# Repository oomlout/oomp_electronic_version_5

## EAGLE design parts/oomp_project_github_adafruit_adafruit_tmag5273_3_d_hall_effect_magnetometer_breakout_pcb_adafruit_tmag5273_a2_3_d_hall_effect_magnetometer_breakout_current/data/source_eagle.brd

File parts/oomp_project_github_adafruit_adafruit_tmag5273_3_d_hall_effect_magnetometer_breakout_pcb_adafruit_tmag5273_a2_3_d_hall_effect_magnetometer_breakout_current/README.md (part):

# Project adafruit/Adafruit-TMAG5273-3D-Hall-Effect-Magnetometer-Breakout-PCB Adafruit TMAG5273 A2 3 D Hall Effect Magnetometer Breakout current

[View the project on GitHub](https://github.com/adafruit/Adafruit-TMAG5273-3D-Hall-Effect-Magnetometer-Breakout-PCB/blob/main/Adafruit%20TMAG5273A2%203D%20Hall%20Effect%20Magnetometer%20Breakout.brd)

[Open the interactive board explorer (GitHub Pages)](https://oomlout.github.io/oomp_electronic_version_5/parts/oomp_project_github_adafruit_adafruit_tmag5273_3_d_hall_effect_magnetometer_breakout_pcb_adafruit_tmag5273_a2_3_d_hall_effect_magnetometer_breakout_current/board_explorer.html)

[Browse this project category](../../navigation/oomp/project/github/adafruit/adafruit_tmag5273_3_d_hall_effect_magnetometer_breakout_pcb/adafruit_tmag5273_a2_3_d_hall_effect_magnetometer_breakout/README.md)

Project adafruit/Adafruit-TMAG5273-3D-Hall-Effect-Magnetometer-Breakout-PCB Adafruit TMAG5273 A2 3 D Hall Effect Magnetometer Breakout current is a KiCad project containing 57 extracted component records. The catalogue matcher linked 14 physical placements to OOMP parts.

## Project snapshot

| Item | Count |
| --- | ---: |
| Components | 57 |
| PCB footprints | 39 |
| Mounting and locating holes | 4 |
| Matched OOMP mounting-hole items | 4 |
| Schematic symbols | 44 |
| Matched OOMP components | 14 |
| Unmatched physical components | 17 |
| Front-side placements | 23 |
| Back-side placements | 4 |
| Project version | `current` |
| Git ref | `main` |

## Board

[Original KiCad files](https://github.com/oomlout/oomp_electronic_version_5/tree/main/parts/oomp_project_github_adafruit_adafruit_tmag5273_3_d_hall_effect_magnetometer_breakout_pcb_adafruit_tmag5273_a2_3_d_hall_effect_magnetometer_breakout_current/data/original) · [OOMP KiCad design and local libraries](https://github.com/oomlout/oomp_electronic_version_5/tree/main/parts/oomp_project_github_adafruit_adafruit_tmag5273_3_d_hall_effect_magnetometer_breakout_pcb_adafruit_tmag5273_a2_3_d_hall_effect_magnetometer_breakout_current/data/oomp_design) · [Conversion / skipped-item report](https://github.com/oomlout/oomp_electronic_version_5/blob/main/parts/oomp_project_github_adafruit_adafruit_tmag5273_3_d_hall_effect_magnetometer_breakout_pcb_adafruit_tmag5273_a2_3_d_hall_effect_magnetometer_breakout_current/data/oomp_design/conversion_report.yaml)

The OOMP design is a separate copy. Only symbols and footprints verified against unchanged installed KiCad masters are replaced; custom and modified items are retained.

- Approximate size: **25.4 mm × 17.78 mm**
- Outline source: `KiCad Edge.Cuts`
- Placement drawing: [view `board.svg`](https://github.com/oomlout/oomp_electronic_version_5/blob/main/parts/oomp_project_github_adafruit_adafruit_tmag5273_3_d_hall_effect_magnetometer_breakout_pcb_adafruit_tmag5273_a2_3_d_hall_effect_magnetometer_breakout_current/data/generated_data/src/board.svg)
- PNG placement drawing: [view `board.png`](https://github.com/oomlout/oomp_electronic_version_5/blob/main/parts/oomp_project_github_adafruit_adafruit_tmag5273_3_d_hall_effect_magnetometer_breakout_pcb_adafruit_tmag5273_a2_3_d_hall_effect_magnetometer_breakout_current/data/generated_data/src/board.png)
- 300-pixel placement preview: [view `board_300.png`](https://github.com/oomlout/oomp_electronic_version_5/blob/main/parts/oomp_project_github_adafruit_adafruit_tmag5273_3_d_hall_effect_magnetometer_breakout_pcb_adafruit_tmag5273_a2_3_d_hall_effect_magnetometer_breakout_current/data/generated_data/src/board_300.png)
- Placement drawing with pin names: [view `board_pins.svg`](https://github.com/oomlout/oomp_electronic_version_5/blob/main/parts/oomp_project_github_adafruit_adafruit_tmag5273_3_d_hall_effect_magnetometer_breakout_pcb_adafruit_tmag5273_a2_3_d_hall_effect_magnetometer_breakout_current/data/generated_data/src/board_pins.svg)
- PNG drawing with pin names: [view `board_pins.png`](https://github.com/oomlout/oomp_electronic_version_5/blob/main/parts/oomp_project_github_adafruit_adafruit_tmag5273_3_d_hall_effect_magnetometer_breakout_pcb_adafruit_tmag5273_a2_3_d_hall_effect_magnetometer_breakout_current/data/generated_data/src/board_pins.png)
- 300-pixel pin preview: [view `board_pins_300.png`](https://github.com/oomlout/oomp_electronic_version_5/blob/main/parts/oomp_project_github_adafruit_adafruit_tmag5273_3_d_hall_effect_magnetometer_breakout_pcb_adafruit_tmag5273_a2_3_d_hall_effect_magnetometer_breakout_current/data/generated_data/src/board_pins_300.png)
- Bottom placement drawing: [view `board_bottom.svg`](https://github.com/oomlout/oomp_electronic_version_5/blob/main/parts/oomp_project_github_adafruit_adafruit_tmag5273_3_d_hall_effect_magnetometer_breakout_pcb_adafruit_tmag5273_a2_3_d_hall_effect_magnetometer_breakout_current/data/generated_data/src/board_bottom.svg)
- Bottom PNG placement drawing: [view `board_bottom.png`](https://github.com/oomlout/oomp_electronic_version_5/blob/main/parts/oomp_project_github_adafruit_adafruit_tmag5273_3_d_hall_effect_magnetometer_breakout_pcb_adafruit_tmag5273_a2_3_d_hall_effect_magnetometer_breakout_current/data/generated_data/src/board_bottom.png)
- 300-pixel bottom preview: [view `board_bottom_300.png`](https://github.com/oomlout/oomp_electronic_version_5/blob/main/parts/oomp_project_github_adafruit_adafruit_tmag5273_3_d_hall_effect_magnetometer_breakout_pcb_adafruit_tmag5273_a2_3_d_hall_effect_magnetometer_breakout_current/data/generated_data/src/board_bottom_300.png)
- Bottom placement drawing with pin names: [view `board_pins_bottom.svg`](https://github.com/oomlout/oomp_electronic_version_5/blob/main/parts/oomp_project_github_adafruit_adafruit_tmag5273_3_d_hall_effect_magnetometer_breakout_pcb_adafruit_tmag5273_a2_3_d_hall_effect_magnetometer_breakout_current/data/generated_data/src/board_pins_bottom.svg)
- Bottom PNG drawing with pin names: [view `board_pins_bottom.png`](https://github.com/oomlout/oomp_electronic_version_5/blob/main/parts/oomp_project_github_adafruit_adafruit_tmag5273_3_d_hall_effect_magnetometer_breakout_pcb_adafruit_tmag5273_a2_3_d_hall_effect_magnetometer_breakout_current/data/generated_data/src/board_pins_bottom.png)
- 300-pixel bottom pin preview: [view `board_pins_bottom_300.png`](https://github.com/oomlout/oomp_electronic_version_5/blob/main/parts/oomp_project_github_adafruit_adafruit_tmag5273_3_d_hall_effect_magnetometer_breakout_pcb_adafruit_tmag5273_a2_3_d_hall_effect_magnetometer_breakout_current/data/generated_data/src/board_pins_bottom_300.png)
- Mechanical drawing: [view `board_mechanical.svg`](https://github.com/oomlout/oomp_electronic_version_5/blob/main/parts/oomp_project_github_adafruit_adafruit_tmag5273_3_d_hall_effect_magnetometer_breakout_pcb_adafruit_tmag5273_a2_3_d_hall_effect_magnetometer_breakout_current/data/generated_data/src/board_mechanical.svg)
- Mechanical PNG: [view `board_mechanical.png`](https://github.com/oomlout/oomp_electronic_version_5/blob/main/parts/oomp_project_github_adafruit_adafruit_tmag5273_3_d_hall_effect_magnetometer_breakout_pcb_adafruit_tmag5273_a2_3_d_hall_effect_magnetometer_breakout_current/data/generated_data/src/board_mechanical.png)
- 300-pixel mechanical preview: [view `board_mechanical_300.png`](https://github.com/oomlout/oomp_electronic_version_5/blob/main/parts/oomp_project_github_adafruit_adafruit_tmag5273_3_d_hall_effect_magnetometer_breakout_pcb_adafruit_tmag5273_a2_3_d_hall_effect_magnetometer_breakout_current/data/generated_data/src/board_mechanical_300.png)
- Open the board explorer on GitHub Pages: [explore this board](https://oomlout.github.io/oomp_electronic_version_5/parts/oomp_project_github_adafruit_adafruit_tmag5273_3_d_hall_effect_magnetometer_breakout_pcb_adafruit_tmag5273_a2_3_d_hall_effect_magnetometer_breakout_current/board_explorer.html)
- InteractiveHtmlBom generation is configured; install KiCad or set `KICAD_PYTHON` to its bundled Python to build `data/interactivehtmlbom/ibom.html`.

## Board with pins

## Bottom board with pins

The bottom view is mirrored horizontally so it is shown as viewed from beneath the assembled board.

## Mechanical layer

The table uses a board-relative origin at the minimum X/Y point of `Edge.Cuts`. This point is shown as **0,0** in the mechanical drawing; X increases right and Y increases down. Original KiCad coordinates are retained alongside it.

### Diameter 2.5 mm holes

| OOMP reference | Source | Name | Classification | Role | Board X (mm) | Board Y (mm) | OOMP part |
| --- | --- | --- | --- | --- | ---: | ---: | --- |
| `MH1` | `U$1` | Mounting Hole 2.5 mm Round Plated | `mechanical / mounting_hole / 2_5_mm / round / plated` | mounting | 2.540 | 2.540 | [`mechanical_mounting_hole_2_5_mm_round_plated`](https://github.com/oomlout/oomp_electronic_version_5/tree/main/parts/mechanical_mounting_hole_2_5_mm_round_plated) |
| `MH2` | `U$17` | Mounting Hole 2.5 mm Round Plated | `mechanical / mounting_hole / 2_5_mm / round / plated` | mounting | 22.860 | 2.540 | [`mechanical_mounting_hole_2_5_mm_round_plated`](https://github.com/oomlout/oomp_electronic_version_5/tree/main/parts/mechanical_mounting_hole_2_5_mm_round_plated) |
| `MH3` | `U$19` | Mounting Hole 2.5 mm Round Plated | `mechanical / mounting_hole / 2_5_mm / round / plated` | mounting | 2.540 | 15.240 | [`mechanical_mounting_hole_2_5_mm_round_plated`](https://github.com/oomlout/oomp_electronic_version_5/tree/main/parts/mechanical_mounting_hole_2_5_mm_round_plated) |
| `MH4` | `U$21` | Mounting Hole 2.5 mm Round Plated | `mechanical / mounting_hole / 2_5_mm / round / plated` | mounting | 22.860 | 15.240 | [`mechanical_mounting_hole_2_5_mm_round_plated`](https://github.com/oomlout/oomp_electronic_version_5/tree/main/parts/mechanical_mounting_hole_2_5_mm_round_plated) |

## Bill of materials

| References | Quantity | Description | Value | Footprint | OOMP part |
| --- | ---: | --- | --- | --- | --- |
| C1 | 1 | Capacitor 100 nF 0603 | 0.1uF | `0603-NO` | [`electronic_capacitor_0603_100_nano_farad`](https://github.com/oomlout/oomp_electronic_version_5/tree/main/parts/electronic_capacitor_0603_100_nano_farad) |
| C2, C3 | 2 | Capacitor 10 uF 0805 | 10uF | `0805-NO` | [`electronic_capacitor_0805_10_micro_farad`](https://github.com/oomlout/oomp_electronic_version_5/tree/main/parts/electronic_capacitor_0805_10_micro_farad) |
| CONN3, CONN4 | 2 | Connector JST Sh SM04B-SRSS-TB | STEMMA_I2C_QT | `JST_SH4` | [`electronic_connector_jst_sh_1_mm_pitch_surface_mount_right_angle_4_pin_jst_sm04b_srss_tb`](https://github.com/oomlout/oomp_electronic_version_5/tree/main/parts/electronic_connector_jst_sh_1_mm_pitch_surface_mount_right_angle_4_pin_jst_sm04b_srss_tb) |
| D1 | 1 | LED Green 0603 | GREEN | `CHIPLED_0603_NOOUTLINE` | [`electronic_led_0603_green`](https://github.com/oomlout/oomp_electronic_version_5/tree/main/parts/electronic_led_0603_green) |
| IC2 | 1 | TMAG5273A2 | TMAG5273A2 | `SOT23-6` | unmatched |
| JP1 | 1 | Connector Header 2.54-1x6P直针 |  | `1X06_ROUND_70` | [`electronic_connector_header_2_54_mm_pitch_through_hole_6_pin`](https://github.com/oomlout/oomp_electronic_version_5/tree/main/parts/electronic_connector_header_2_54_mm_pitch_through_hole_6_pin) |
| PLABEL0 | 1 | PLABEL0 |  | `PLABEL0` | unmatched |
| PLABEL1 | 1 | PLABEL1 |  | `PLABEL1` | unmatched |
| PLABEL2 | 1 | PLABEL2 |  | `PLABEL2` | unmatched |
| PLABEL3 | 1 | PLABEL3 |  | `PLABEL3` | unmatched |
| PLABEL4 | 1 | PLABEL4 |  | `PLABEL4` | unmatched |
| PLABEL6 | 1 | PLABEL6 |  | `PLABEL6` | unmatched |
| PLABEL7 | 1 | PLABEL7 |  | `PLABEL7` | unmatched |
| PLABEL8 | 1 | PLABEL8 |  | `PLABEL8` | unmatched |
| PLABEL9 | 1 | PLABEL9 |  | `PLABEL9` | unmatched |
| PLABEL10 | 1 | PLABEL10 |  | `PLABEL10` | unmatched |
| PLABEL13 | 1 | PLABEL13 |  | `PLABEL13` | unmatched |
| PLABEL14 | 1 | PLABEL14 |  | `PLABEL14` | unmatched |
| PLABEL15 | 1 | PLABEL15 |  | `PLABEL15` | unmatched |
| PLABEL16 | 1 | PLABEL16 |  | `PLABEL16` | unmatched |
| PLABEL17 | 1 | PLABEL17 |  | `PLABEL17` | unmatched |
| Q2 | 1 | Transistor Mosfet N Channel Dual SOT 363 6 | BSS138 | `SOT363` | [`electronic_transistor_sot_363_6_mosfet_n_channel_dual`](https://github.com/oomlout/oomp_electronic_version_5/tree/main/parts/electronic_transistor_sot_363_6_mosfet_n_channel_dual) |
| R1 | 1 | Resistor 10000 Ohm 0603 | 10K | `0603-NO` | [`electronic_resistor_0603_10000_ohm`](https://github.com/oomlout/oomp_electronic_version_5/tree/main/parts/electronic_resistor_0603_10000_ohm) |
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
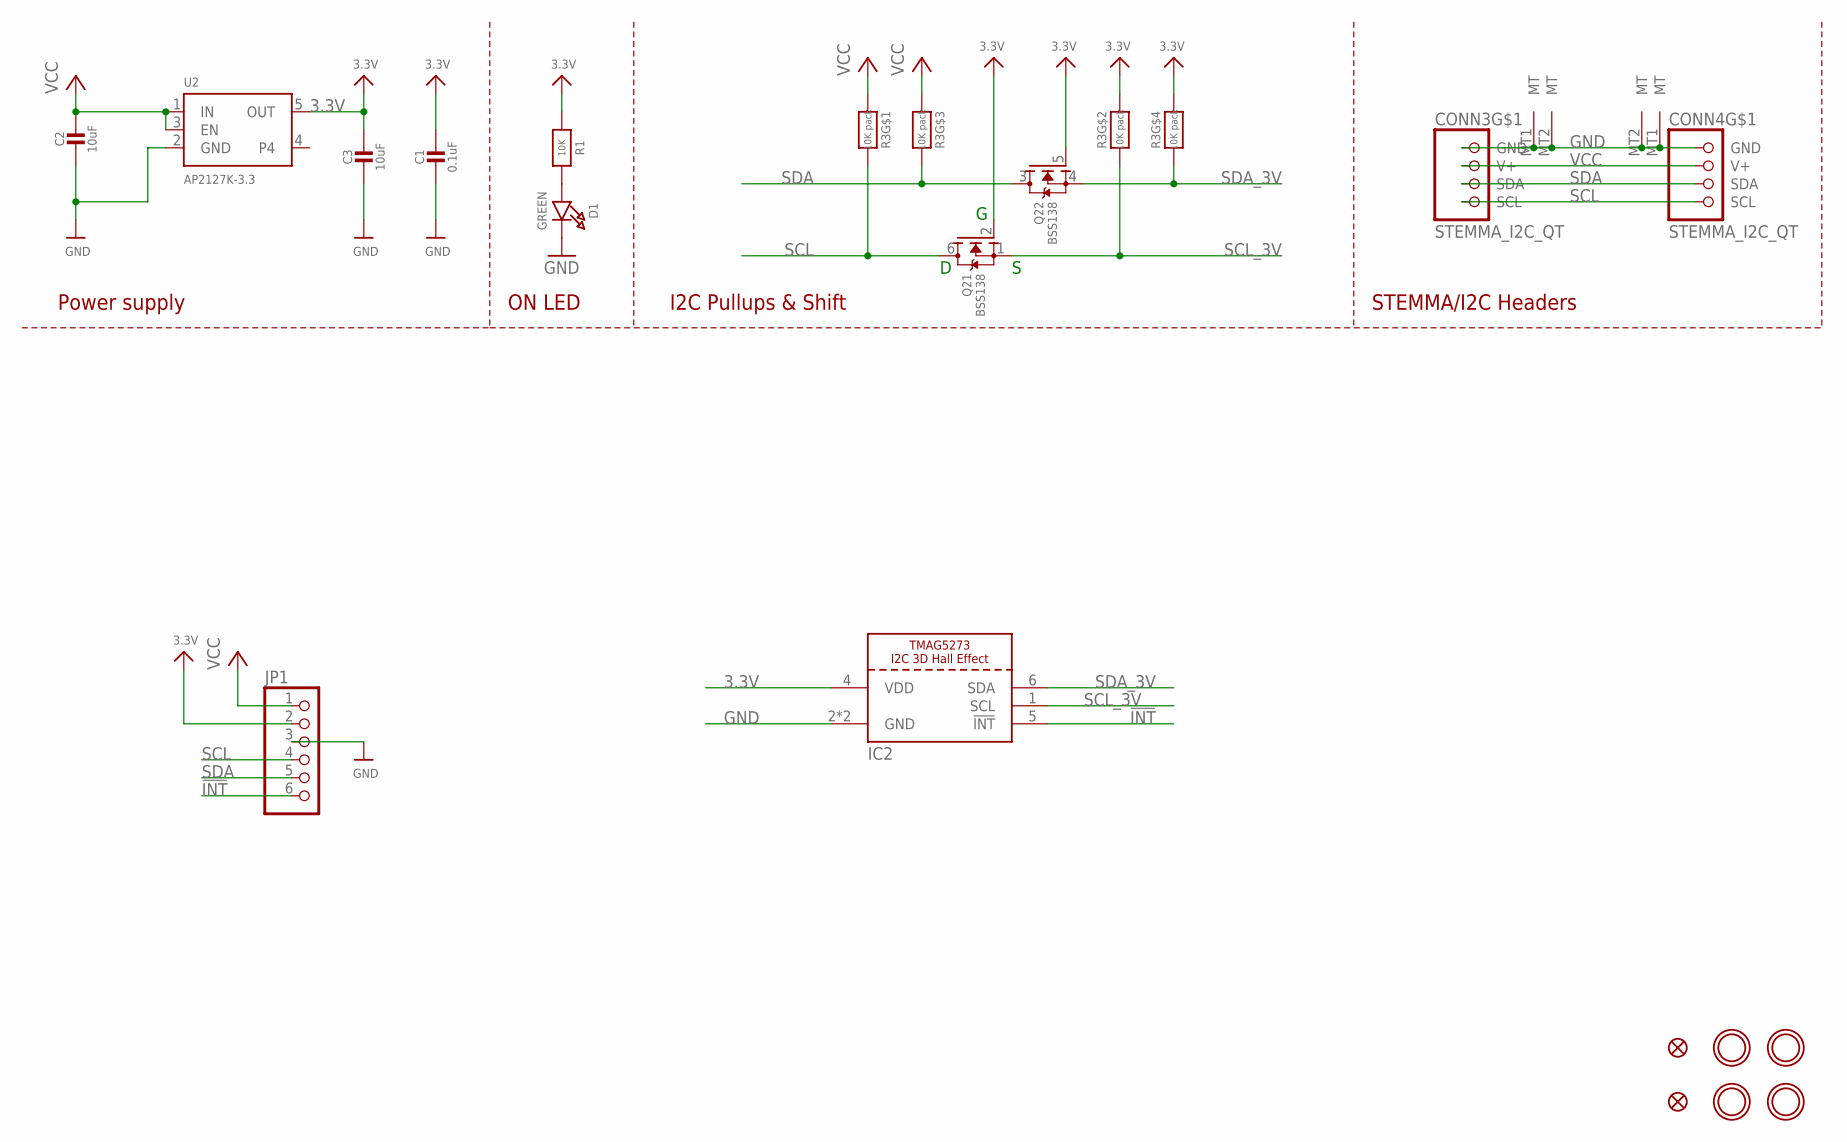
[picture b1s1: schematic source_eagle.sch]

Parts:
C1: 0.1uF; 0603-NO
C2, C3: 10uF; 0805-NO
CONN3, CONN4: STEMMA_I2C_QT; JST_SH4
D1: GREEN; CHIPLED_0603_NOOUTLINE
FID3, FID4: FIDUCIAL_0.5MM
IC2: TMAG5273A2; SOT23-6
JP1: HEADER-1X670MIL; 1X06_ROUND_70
Q2: BSS138; SOT363
R1: 10K; 0603-NO
R3: 10K pack; RESPACK_4X0603
U2: AP2127K-3.3; SOT23-5
U$1, U$17, U$19, U$21: MOUNTINGHOLE2.5; MOUNTINGHOLE_2.5_PLATED

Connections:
3.3V: C1.1, C3.1, IC2.4 (VDD), JP1.2, Q2.2 (G), Q2.5 (G), R1.1, R3.2 (1), R3.4 (1), U2.5 (OUT)
!INT: IC2.5 (!INT), JP1.6
GND: C1.2, C2.2, C3.2, CONN3.1 (GND), CONN3.MT1 (MT), CONN3.MT2 (MT), CONN4.1 (GND), CONN4.MT1 (MT), CONN4.MT2 (MT), D1.C, IC2.2 (GND), IC2.3 (GND), JP1.3, U2.2 (GND)
unnamed: D1.A, R1.2
SCL: CONN3.4 (SCL), CONN4.4 (SCL), JP1.4, Q2.6 (D), R3.8 (2)
SCL_3V: IC2.1 (SCL), Q2.1 (S), R3.7 (2)
SDA: CONN3.3 (SDA), CONN4.3 (SDA), JP1.5, Q2.3 (D), R3.6 (2)
SDA_3V: IC2.6 (SDA), Q2.4 (S), R3.5 (2)
VCC: C2.1, CONN3.2 (V+), CONN4.2 (V+), JP1.1, R3.1, R3.3 (1), U2.1 (IN), U2.3 (EN)

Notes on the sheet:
I2C Pullups & Shift
STEMMA/I2C Headers
ON LED
Power supply

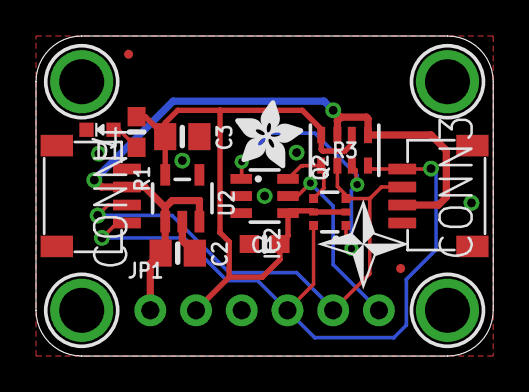
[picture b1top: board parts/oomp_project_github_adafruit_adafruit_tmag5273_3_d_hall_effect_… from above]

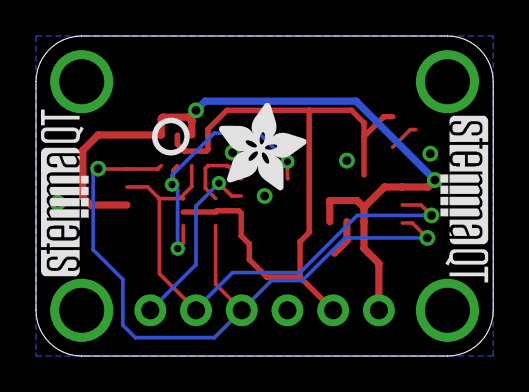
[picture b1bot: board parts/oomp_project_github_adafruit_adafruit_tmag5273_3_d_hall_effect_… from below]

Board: 2 copper layers, 25.4 x 17.8 mm, 39 parts (8 on the bottom side), 9 nets.

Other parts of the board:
PLABEL0: PLABEL0
PLABEL1: PLABEL1
PLABEL2: PLABEL2
PLABEL3: PLABEL3
PLABEL4: PLABEL4
PLABEL6: PLABEL6
PLABEL7: PLABEL7
PLABEL8: PLABEL8
PLABEL9: PLABEL9
PLABEL10: PLABEL10
PLABEL13: PLABEL13
PLABEL14: PLABEL14
PLABEL15: PLABEL15
PLABEL16: PLABEL16
PLABEL17: PLABEL17
U$2: SYMBOL_COMPASSXY_5MM
U$4: ADAFRUIT_5MM
U$22: ADAFRUIT_3.5MM
U$25: PCBFEAT-REV-040
U$30, U$31: STEMMAQT

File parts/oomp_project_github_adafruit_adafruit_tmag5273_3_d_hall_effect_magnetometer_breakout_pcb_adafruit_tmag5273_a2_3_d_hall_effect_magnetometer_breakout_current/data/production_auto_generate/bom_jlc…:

Comment,Designator,Footprint,LCSC Part #
,JP1,1X06_ROUND_70,C37208
,U$22,ADAFRUIT_3.5MM,
,U$4,ADAFRUIT_5MM,
,U$25,PCBFEAT-REV-040,
,PLABEL0,PLABEL0,
,PLABEL1,PLABEL1,
,PLABEL10,PLABEL10,
,PLABEL13,PLABEL13,
,PLABEL14,PLABEL14,
,PLABEL15,PLABEL15,
,PLABEL16,PLABEL16,
,PLABEL17,PLABEL17,
,PLABEL2,PLABEL2,
,PLABEL3,PLABEL3,
,PLABEL4,PLABEL4,
,PLABEL6,PLABEL6,
,PLABEL7,PLABEL7,
,PLABEL8,PLABEL8,
,PLABEL9,PLABEL9,
,"U$30,U$31",STEMMAQT,
,U$2,SYMBOL_COMPASSXY_5MM,
0.1uF,C1,0603-NO,C14663
10K,R1,0603-NO,C98220
10K pack,R3,RESPACK_4X0603,C98220
10uF,"C2,C3",0805-NO,
AP2127K-3.3,U2,SOT23-5,
BSS138,Q2,SOT363,
GREEN,D1,CHIPLED_0603_NOOUTLINE,
STEMMA_I2C_QT,"CONN3,CONN4",JST_SH4,C160404
TMAG5273A2,IC2,SOT23-6,

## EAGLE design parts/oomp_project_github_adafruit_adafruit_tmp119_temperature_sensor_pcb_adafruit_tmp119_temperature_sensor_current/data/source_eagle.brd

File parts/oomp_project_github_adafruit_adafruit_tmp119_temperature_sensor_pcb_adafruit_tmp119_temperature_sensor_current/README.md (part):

# Project adafruit/Adafruit-TMP119-Temperature-Sensor-PCB Adafruit TMP119 Temperature Sensor current

[View the project on GitHub](https://github.com/adafruit/Adafruit-TMP119-Temperature-Sensor-PCB/blob/main/Adafruit%20TMP119%20Temperature%20Sensor.brd)

[Open the interactive board explorer (GitHub Pages)](https://oomlout.github.io/oomp_electronic_version_5/parts/oomp_project_github_adafruit_adafruit_tmp119_temperature_sensor_pcb_adafruit_tmp119_temperature_sensor_current/board_explorer.html)

[Browse this project category](../../navigation/oomp/project/github/adafruit/adafruit_tmp119_temperature_sensor_pcb/adafruit_tmp119_temperature_sensor/README.md)

Project adafruit/Adafruit-TMP119-Temperature-Sensor-PCB Adafruit TMP119 Temperature Sensor current is a KiCad project containing 53 extracted component records. The catalogue matcher linked 12 physical placements to OOMP parts.

## Project snapshot

| Item | Count |
| --- | ---: |
| Components | 53 |
| PCB footprints | 37 |
| Mounting and locating holes | 4 |
| Matched OOMP mounting-hole items | 4 |
| Schematic symbols | 40 |
| Matched OOMP components | 12 |
| Unmatched physical components | 17 |
| Front-side placements | 18 |
| Back-side placements | 7 |
| Project version | `current` |
| Git ref | `main` |

## Board

[Original KiCad files](https://github.com/oomlout/oomp_electronic_version_5/tree/main/parts/oomp_project_github_adafruit_adafruit_tmp119_temperature_sensor_pcb_adafruit_tmp119_temperature_sensor_current/data/original) · [OOMP KiCad design and local libraries](https://github.com/oomlout/oomp_electronic_version_5/tree/main/parts/oomp_project_github_adafruit_adafruit_tmp119_temperature_sensor_pcb_adafruit_tmp119_temperature_sensor_current/data/oomp_design) · [Conversion / skipped-item report](https://github.com/oomlout/oomp_electronic_version_5/blob/main/parts/oomp_project_github_adafruit_adafruit_tmp119_temperature_sensor_pcb_adafruit_tmp119_temperature_sensor_current/data/oomp_design/conversion_report.yaml)

The OOMP design is a separate copy. Only symbols and footprints verified against unchanged installed KiCad masters are replaced; custom and modified items are retained.

- Approximate size: **25.4 mm × 17.78 mm**
- Outline source: `KiCad Edge.Cuts`
- Placement drawing: [view `board.svg`](https://github.com/oomlout/oomp_electronic_version_5/blob/main/parts/oomp_project_github_adafruit_adafruit_tmp119_temperature_sensor_pcb_adafruit_tmp119_temperature_sensor_current/data/generated_data/src/board.svg)
- PNG placement drawing: [view `board.png`](https://github.com/oomlout/oomp_electronic_version_5/blob/main/parts/oomp_project_github_adafruit_adafruit_tmp119_temperature_sensor_pcb_adafruit_tmp119_temperature_sensor_current/data/generated_data/src/board.png)
- 300-pixel placement preview: [view `board_300.png`](https://github.com/oomlout/oomp_electronic_version_5/blob/main/parts/oomp_project_github_adafruit_adafruit_tmp119_temperature_sensor_pcb_adafruit_tmp119_temperature_sensor_current/data/generated_data/src/board_300.png)
- Placement drawing with pin names: [view `board_pins.svg`](https://github.com/oomlout/oomp_electronic_version_5/blob/main/parts/oomp_project_github_adafruit_adafruit_tmp119_temperature_sensor_pcb_adafruit_tmp119_temperature_sensor_current/data/generated_data/src/board_pins.svg)
- PNG drawing with pin names: [view `board_pins.png`](https://github.com/oomlout/oomp_electronic_version_5/blob/main/parts/oomp_project_github_adafruit_adafruit_tmp119_temperature_sensor_pcb_adafruit_tmp119_temperature_sensor_current/data/generated_data/src/board_pins.png)
- 300-pixel pin preview: [view `board_pins_300.png`](https://github.com/oomlout/oomp_electronic_version_5/blob/main/parts/oomp_project_github_adafruit_adafruit_tmp119_temperature_sensor_pcb_adafruit_tmp119_temperature_sensor_current/data/generated_data/src/board_pins_300.png)
- Bottom placement drawing: [view `board_bottom.svg`](https://github.com/oomlout/oomp_electronic_version_5/blob/main/parts/oomp_project_github_adafruit_adafruit_tmp119_temperature_sensor_pcb_adafruit_tmp119_temperature_sensor_current/data/generated_data/src/board_bottom.svg)
- Bottom PNG placement drawing: [view `board_bottom.png`](https://github.com/oomlout/oomp_electronic_version_5/blob/main/parts/oomp_project_github_adafruit_adafruit_tmp119_temperature_sensor_pcb_adafruit_tmp119_temperature_sensor_current/data/generated_data/src/board_bottom.png)
- 300-pixel bottom preview: [view `board_bottom_300.png`](https://github.com/oomlout/oomp_electronic_version_5/blob/main/parts/oomp_project_github_adafruit_adafruit_tmp119_temperature_sensor_pcb_adafruit_tmp119_temperature_sensor_current/data/generated_data/src/board_bottom_300.png)
- Bottom placement drawing with pin names: [view `board_pins_bottom.svg`](https://github.com/oomlout/oomp_electronic_version_5/blob/main/parts/oomp_project_github_adafruit_adafruit_tmp119_temperature_sensor_pcb_adafruit_tmp119_temperature_sensor_current/data/generated_data/src/board_pins_bottom.svg)
- Bottom PNG drawing with pin names: [view `board_pins_bottom.png`](https://github.com/oomlout/oomp_electronic_version_5/blob/main/parts/oomp_project_github_adafruit_adafruit_tmp119_temperature_sensor_pcb_adafruit_tmp119_temperature_sensor_current/data/generated_data/src/board_pins_bottom.png)
- 300-pixel bottom pin preview: [view `board_pins_bottom_300.png`](https://github.com/oomlout/oomp_electronic_version_5/blob/main/parts/oomp_project_github_adafruit_adafruit_tmp119_temperature_sensor_pcb_adafruit_tmp119_temperature_sensor_current/data/generated_data/src/board_pins_bottom_300.png)
- Mechanical drawing: [view `board_mechanical.svg`](https://github.com/oomlout/oomp_electronic_version_5/blob/main/parts/oomp_project_github_adafruit_adafruit_tmp119_temperature_sensor_pcb_adafruit_tmp119_temperature_sensor_current/data/generated_data/src/board_mechanical.svg)
- Mechanical PNG: [view `board_mechanical.png`](https://github.com/oomlout/oomp_electronic_version_5/blob/main/parts/oomp_project_github_adafruit_adafruit_tmp119_temperature_sensor_pcb_adafruit_tmp119_temperature_sensor_current/data/generated_data/src/board_mechanical.png)
- 300-pixel mechanical preview: [view `board_mechanical_300.png`](https://github.com/oomlout/oomp_electronic_version_5/blob/main/parts/oomp_project_github_adafruit_adafruit_tmp119_temperature_sensor_pcb_adafruit_tmp119_temperature_sensor_current/data/generated_data/src/board_mechanical_300.png)
- Open the board explorer on GitHub Pages: [explore this board](https://oomlout.github.io/oomp_electronic_version_5/parts/oomp_project_github_adafruit_adafruit_tmp119_temperature_sensor_pcb_adafruit_tmp119_temperature_sensor_current/board_explorer.html)
- InteractiveHtmlBom generation is configured; install KiCad or set `KICAD_PYTHON` to its bundled Python to build `data/interactivehtmlbom/ibom.html`.

## Board with pins

## Bottom board with pins

The bottom view is mirrored horizontally so it is shown as viewed from beneath the assembled board.

## Mechanical layer

The table uses a board-relative origin at the minimum X/Y point of `Edge.Cuts`. This point is shown as **0,0** in the mechanical drawing; X increases right and Y increases down. Original KiCad coordinates are retained alongside it.

### Diameter 2.5 mm holes

| OOMP reference | Source | Name | Classification | Role | Board X (mm) | Board Y (mm) | OOMP part |
| --- | --- | --- | --- | --- | ---: | ---: | --- |
| `MH1` | `U$1` | Mounting Hole 2.5 mm Round Plated | `mechanical / mounting_hole / 2_5_mm / round / plated` | mounting | 2.540 | 2.540 | [`mechanical_mounting_hole_2_5_mm_round_plated`](https://github.com/oomlout/oomp_electronic_version_5/tree/main/parts/mechanical_mounting_hole_2_5_mm_round_plated) |
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
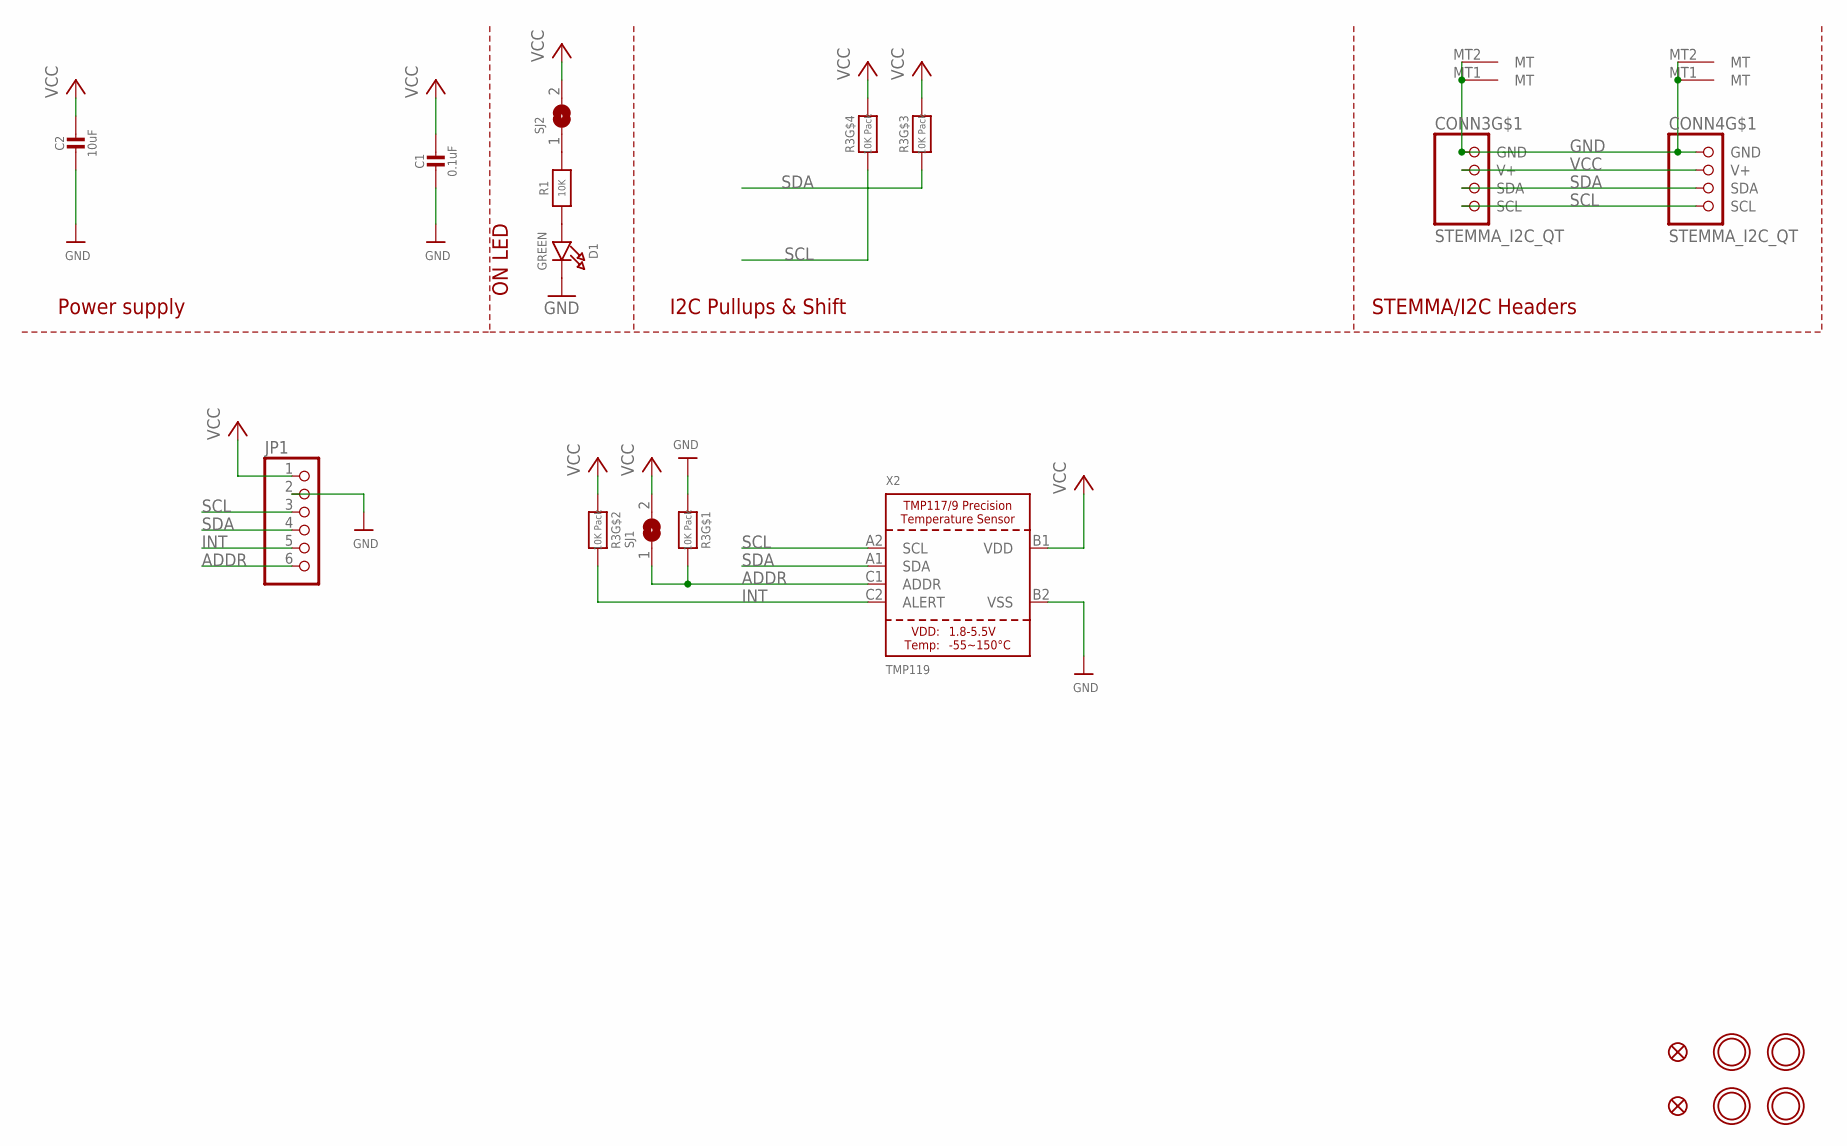
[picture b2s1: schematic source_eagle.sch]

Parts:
C1: 0.1uF; 0603-NO
C2: 10uF; 0805-NO
CONN3, CONN4: STEMMA_I2C_QT; JST_SH4
D1: GREEN; CHIPLED_0603_NOOUTLINE
FID3, FID4: FIDUCIAL_0.5MM
JP1: HEADER-1X670MIL; 1X06_ROUND_70
R1: 10K; 0603-NO
R3: 10K Pack; RESPACK_4X0603
SJ1: SOLDERJUMPER; SOLDERJUMPER_ARROW_NOPASTE
SJ2: SOLDERJUMPERCLOSED; SOLDERJUMPER_CLOSEDWIRE
U$1, U$17, U$19, U$21: MOUNTINGHOLE2.5; MOUNTINGHOLE_2.5_PLATED
X2: TMP119; DSBGA-9

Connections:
ADDR: JP1.6, R3.8 (2), SJ1.1, X2.C1 (ADDR)
GND: C1.2, C2.2, CONN3.1 (GND), CONN3.MT1 (MT), CONN3.MT2 (MT), CONN4.1 (GND), CONN4.MT1 (MT), CONN4.MT2 (MT), D1.C, JP1.2, R3.1, X2.B2 (VSS)
INT: JP1.5, R3.7 (2), X2.C2 (ALERT)
unnamed: D1.A, R1.1
unnamed: R1.2, SJ2.1
SCL: CONN3.4 (SCL), CONN4.4 (SCL), JP1.3, R3.4 (1), X2.A2 (SCL)
SDA: CONN3.3 (SDA), CONN4.3 (SDA), JP1.4, R3.3 (1), X2.A1 (SDA)
VCC: C1.1, C2.1, CONN3.2 (V+), CONN4.2 (V+), JP1.1, R3.2 (1), R3.5 (2), R3.6 (2), SJ1.2, SJ2.2, X2.B1 (VDD)

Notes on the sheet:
I2C Pullups & Shift
STEMMA/I2C Headers
ON LED
Power supply

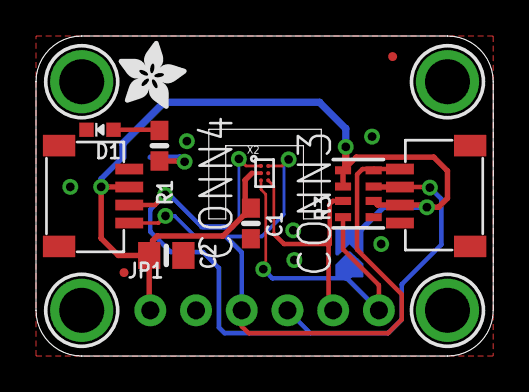
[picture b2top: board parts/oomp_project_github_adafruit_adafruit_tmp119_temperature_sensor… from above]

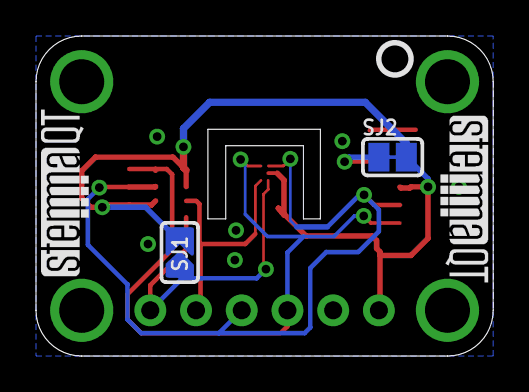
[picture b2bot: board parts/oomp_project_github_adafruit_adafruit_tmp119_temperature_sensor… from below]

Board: 2 copper layers, 25.4 x 17.8 mm, 37 parts (12 on the bottom side), 8 nets.

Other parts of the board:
PLABEL0: PLABEL0
PLABEL1: PLABEL1
PLABEL2: PLABEL2
PLABEL3: PLABEL3
PLABEL4: PLABEL4
PLABEL5: PLABEL5
PLABEL6: PLABEL6
PLABEL7: PLABEL7
PLABEL8: PLABEL8
PLABEL9: PLABEL9
PLABEL10: PLABEL10
PLABEL11: PLABEL11
PLABEL12: PLABEL12
PLABEL13: PLABEL13
PLABEL14: PLABEL14
PLABEL15: PLABEL15
U$22: ADAFRUIT_3.5MM
U$25: PCBFEAT-REV-040
U$30, U$31: STEMMAQT

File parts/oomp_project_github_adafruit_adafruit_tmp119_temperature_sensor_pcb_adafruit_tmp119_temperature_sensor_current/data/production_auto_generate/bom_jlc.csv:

Comment,Designator,Footprint,LCSC Part #
,JP1,Adafruit TMP119 Temperature Sensor-import-fps:1X06_ROUND_70,C37208
,U$22,Adafruit TMP119 Temperature Sensor-import-fps:ADAFRUIT_3.5MM,
,U$25,Adafruit TMP119 Temperature Sensor-import-fps:PCBFEAT-REV-040,
,PLABEL0,Adafruit TMP119 Temperature Sensor-import-fps:PLABEL0,
,PLABEL1,Adafruit TMP119 Temperature Sensor-import-fps:PLABEL1,
,PLABEL10,Adafruit TMP119 Temperature Sensor-import-fps:PLABEL10,
,PLABEL11,Adafruit TMP119 Temperature Sensor-import-fps:PLABEL11,
,PLABEL12,Adafruit TMP119 Temperature Sensor-import-fps:PLABEL12,
,PLABEL13,Adafruit TMP119 Temperature Sensor-import-fps:PLABEL13,
,PLABEL14,Adafruit TMP119 Temperature Sensor-import-fps:PLABEL14,
,PLABEL15,Adafruit TMP119 Temperature Sensor-import-fps:PLABEL15,
,PLABEL2,Adafruit TMP119 Temperature Sensor-import-fps:PLABEL2,
,PLABEL3,Adafruit TMP119 Temperature Sensor-import-fps:PLABEL3,
,PLABEL4,Adafruit TMP119 Temperature Sensor-import-fps:PLABEL4,
,PLABEL5,Adafruit TMP119 Temperature Sensor-import-fps:PLABEL5,
,PLABEL6,Adafruit TMP119 Temperature Sensor-import-fps:PLABEL6,
,PLABEL7,Adafruit TMP119 Temperature Sensor-import-fps:PLABEL7,
,PLABEL8,Adafruit TMP119 Temperature Sensor-import-fps:PLABEL8,
,PLABEL9,Adafruit TMP119 Temperature Sensor-import-fps:PLABEL9,
,"U$30,U$31",Adafruit TMP119 Temperature Sensor-import-fps:STEMMAQT,
0.1uF,C1,Adafruit TMP119 Temperature Sensor-import-fps:0603-NO,C14663
10K,R1,Adafruit TMP119 Temperature Sensor-import-fps:0603-NO,C98220
10K Pack,R3,Adafruit TMP119 Temperature Sensor-import-fps:RESPACK_4X0603,C98220
10uF,C2,Adafruit TMP119 Temperature Sensor-import-fps:0805-NO,
GREEN,D1,Adafruit TMP119 Temperature Sensor-import-fps:CHIPLED_0603_NOOUTLINE,
STEMMA_I2C_QT,"CONN3,CONN4",Adafruit TMP119 Temperature Sensor-import-fps:JST_SH4,C160404
TMP119,X2,Adafruit TMP119 Temperature Sensor-import-fps:DSBGA-9,

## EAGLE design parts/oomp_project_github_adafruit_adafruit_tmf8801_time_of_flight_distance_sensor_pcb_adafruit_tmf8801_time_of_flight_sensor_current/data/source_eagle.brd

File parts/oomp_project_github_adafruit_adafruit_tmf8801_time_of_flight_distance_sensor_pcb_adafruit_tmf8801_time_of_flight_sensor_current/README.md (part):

# Project adafruit/Adafruit-TMF8801-Time-of-Flight-Distance-Sensor-PCB Adafruit TMF8801 Time of Flight Sensor current

[View the project on GitHub](https://github.com/adafruit/Adafruit-TMF8801-Time-of-Flight-Distance-Sensor-PCB/blob/main/Adafruit%20TMF8801%20Time%20of%20Flight%20Sensor%20rev%20B.brd)

[Open the interactive board explorer (GitHub Pages)](https://oomlout.github.io/oomp_electronic_version_5/parts/oomp_project_github_adafruit_adafruit_tmf8801_time_of_flight_distance_sensor_pcb_adafruit_tmf8801_time_of_flight_sensor_current/board_explorer.html)

[Browse this project category](../../navigation/oomp/project/github/adafruit/adafruit_tmf8801_time_of_flight_distance_sensor_pcb/adafruit_tmf8801_time_of_flight_sensor/README.md)

Project adafruit/Adafruit-TMF8801-Time-of-Flight-Distance-Sensor-PCB Adafruit TMF8801 Time of Flight Sensor current is a KiCad project containing 70 extracted component records. The catalogue matcher linked 20 physical placements to OOMP parts.

## Project snapshot

| Item | Count |
| --- | ---: |
| Components | 70 |
| PCB footprints | 43 |
| Mounting and locating holes | 4 |
| Matched OOMP mounting-hole items | 4 |
| Schematic symbols | 61 |
| Matched OOMP components | 20 |
| Unmatched physical components | 16 |
| Front-side placements | 28 |
| Back-side placements | 4 |
| Project version | `current` |
| Git ref | `main` |

## Board

[Original KiCad files](https://github.com/oomlout/oomp_electronic_version_5/tree/main/parts/oomp_project_github_adafruit_adafruit_tmf8801_time_of_flight_distance_sensor_pcb_adafruit_tmf8801_time_of_flight_sensor_current/data/original) · [OOMP KiCad design and local libraries](https://github.com/oomlout/oomp_electronic_version_5/tree/main/parts/oomp_project_github_adafruit_adafruit_tmf8801_time_of_flight_distance_sensor_pcb_adafruit_tmf8801_time_of_flight_sensor_current/data/oomp_design) · [Conversion / skipped-item report](https://github.com/oomlout/oomp_electronic_version_5/blob/main/parts/oomp_project_github_adafruit_adafruit_tmf8801_time_of_flight_distance_sensor_pcb_adafruit_tmf8801_time_of_flight_sensor_current/data/oomp_design/conversion_report.yaml)

The OOMP design is a separate copy. Only symbols and footprints verified against unchanged installed KiCad masters are replaced; custom and modified items are retained.

- Approximate size: **25.4 mm × 17.78 mm**
- Outline source: `KiCad Edge.Cuts`
- Placement drawing: [view `board.svg`](https://github.com/oomlout/oomp_electronic_version_5/blob/main/parts/oomp_project_github_adafruit_adafruit_tmf8801_time_of_flight_distance_sensor_pcb_adafruit_tmf8801_time_of_flight_sensor_current/data/generated_data/src/board.svg)
- PNG placement drawing: [view `board.png`](https://github.com/oomlout/oomp_electronic_version_5/blob/main/parts/oomp_project_github_adafruit_adafruit_tmf8801_time_of_flight_distance_sensor_pcb_adafruit_tmf8801_time_of_flight_sensor_current/data/generated_data/src/board.png)
- 300-pixel placement preview: [view `board_300.png`](https://github.com/oomlout/oomp_electronic_version_5/blob/main/parts/oomp_project_github_adafruit_adafruit_tmf8801_time_of_flight_distance_sensor_pcb_adafruit_tmf8801_time_of_flight_sensor_current/data/generated_data/src/board_300.png)
- Placement drawing with pin names: [view `board_pins.svg`](https://github.com/oomlout/oomp_electronic_version_5/blob/main/parts/oomp_project_github_adafruit_adafruit_tmf8801_time_of_flight_distance_sensor_pcb_adafruit_tmf8801_time_of_flight_sensor_current/data/generated_data/src/board_pins.svg)
- PNG drawing with pin names: [view `board_pins.png`](https://github.com/oomlout/oomp_electronic_version_5/blob/main/parts/oomp_project_github_adafruit_adafruit_tmf8801_time_of_flight_distance_sensor_pcb_adafruit_tmf8801_time_of_flight_sensor_current/data/generated_data/src/board_pins.png)
- 300-pixel pin preview: [view `board_pins_300.png`](https://github.com/oomlout/oomp_electronic_version_5/blob/main/parts/oomp_project_github_adafruit_adafruit_tmf8801_time_of_flight_distance_sensor_pcb_adafruit_tmf8801_time_of_flight_sensor_current/data/generated_data/src/board_pins_300.png)
- Bottom placement drawing: [view `board_bottom.svg`](https://github.com/oomlout/oomp_electronic_version_5/blob/main/parts/oomp_project_github_adafruit_adafruit_tmf8801_time_of_flight_distance_sensor_pcb_adafruit_tmf8801_time_of_flight_sensor_current/data/generated_data/src/board_bottom.svg)
- Bottom PNG placement drawing: [view `board_bottom.png`](https://github.com/oomlout/oomp_electronic_version_5/blob/main/parts/oomp_project_github_adafruit_adafruit_tmf8801_time_of_flight_distance_sensor_pcb_adafruit_tmf8801_time_of_flight_sensor_current/data/generated_data/src/board_bottom.png)
- 300-pixel bottom preview: [view `board_bottom_300.png`](https://github.com/oomlout/oomp_electronic_version_5/blob/main/parts/oomp_project_github_adafruit_adafruit_tmf8801_time_of_flight_distance_sensor_pcb_adafruit_tmf8801_time_of_flight_sensor_current/data/generated_data/src/board_bottom_300.png)
- Bottom placement drawing with pin names: [view `board_pins_bottom.svg`](https://github.com/oomlout/oomp_electronic_version_5/blob/main/parts/oomp_project_github_adafruit_adafruit_tmf8801_time_of_flight_distance_sensor_pcb_adafruit_tmf8801_time_of_flight_sensor_current/data/generated_data/src/board_pins_bottom.svg)
- Bottom PNG drawing with pin names: [view `board_pins_bottom.png`](https://github.com/oomlout/oomp_electronic_version_5/blob/main/parts/oomp_project_github_adafruit_adafruit_tmf8801_time_of_flight_distance_sensor_pcb_adafruit_tmf8801_time_of_flight_sensor_current/data/generated_data/src/board_pins_bottom.png)
- 300-pixel bottom pin preview: [view `board_pins_bottom_300.png`](https://github.com/oomlout/oomp_electronic_version_5/blob/main/parts/oomp_project_github_adafruit_adafruit_tmf8801_time_of_flight_distance_sensor_pcb_adafruit_tmf8801_time_of_flight_sensor_current/data/generated_data/src/board_pins_bottom_300.png)
- Mechanical drawing: [view `board_mechanical.svg`](https://github.com/oomlout/oomp_electronic_version_5/blob/main/parts/oomp_project_github_adafruit_adafruit_tmf8801_time_of_flight_distance_sensor_pcb_adafruit_tmf8801_time_of_flight_sensor_current/data/generated_data/src/board_mechanical.svg)
- Mechanical PNG: [view `board_mechanical.png`](https://github.com/oomlout/oomp_electronic_version_5/blob/main/parts/oomp_project_github_adafruit_adafruit_tmf8801_time_of_flight_distance_sensor_pcb_adafruit_tmf8801_time_of_flight_sensor_current/data/generated_data/src/board_mechanical.png)
- 300-pixel mechanical preview: [view `board_mechanical_300.png`](https://github.com/oomlout/oomp_electronic_version_5/blob/main/parts/oomp_project_github_adafruit_adafruit_tmf8801_time_of_flight_distance_sensor_pcb_adafruit_tmf8801_time_of_flight_sensor_current/data/generated_data/src/board_mechanical_300.png)
- Open the board explorer on GitHub Pages: [explore this board](https://oomlout.github.io/oomp_electronic_version_5/parts/oomp_project_github_adafruit_adafruit_tmf8801_time_of_flight_distance_sensor_pcb_adafruit_tmf8801_time_of_flight_sensor_current/board_explorer.html)
- InteractiveHtmlBom generation is configured; install KiCad or set `KICAD_PYTHON` to its bundled Python to build `data/interactivehtmlbom/ibom.html`.

## Board with pins

## Bottom board with pins

The bottom view is mirrored horizontally so it is shown as viewed from beneath the assembled board.

## Mechanical layer

The table uses a board-relative origin at the minimum X/Y point of `Edge.Cuts`. This point is shown as **0,0** in the mechanical drawing; X increases right and Y increases down. Original KiCad coordinates are retained alongside it.

### Diameter 2.5 mm holes

| OOMP reference | Source | Name | Classification | Role | Board X (mm) | Board Y (mm) | OOMP part |
| --- | --- | --- | --- | --- | ---: | ---: | --- |
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
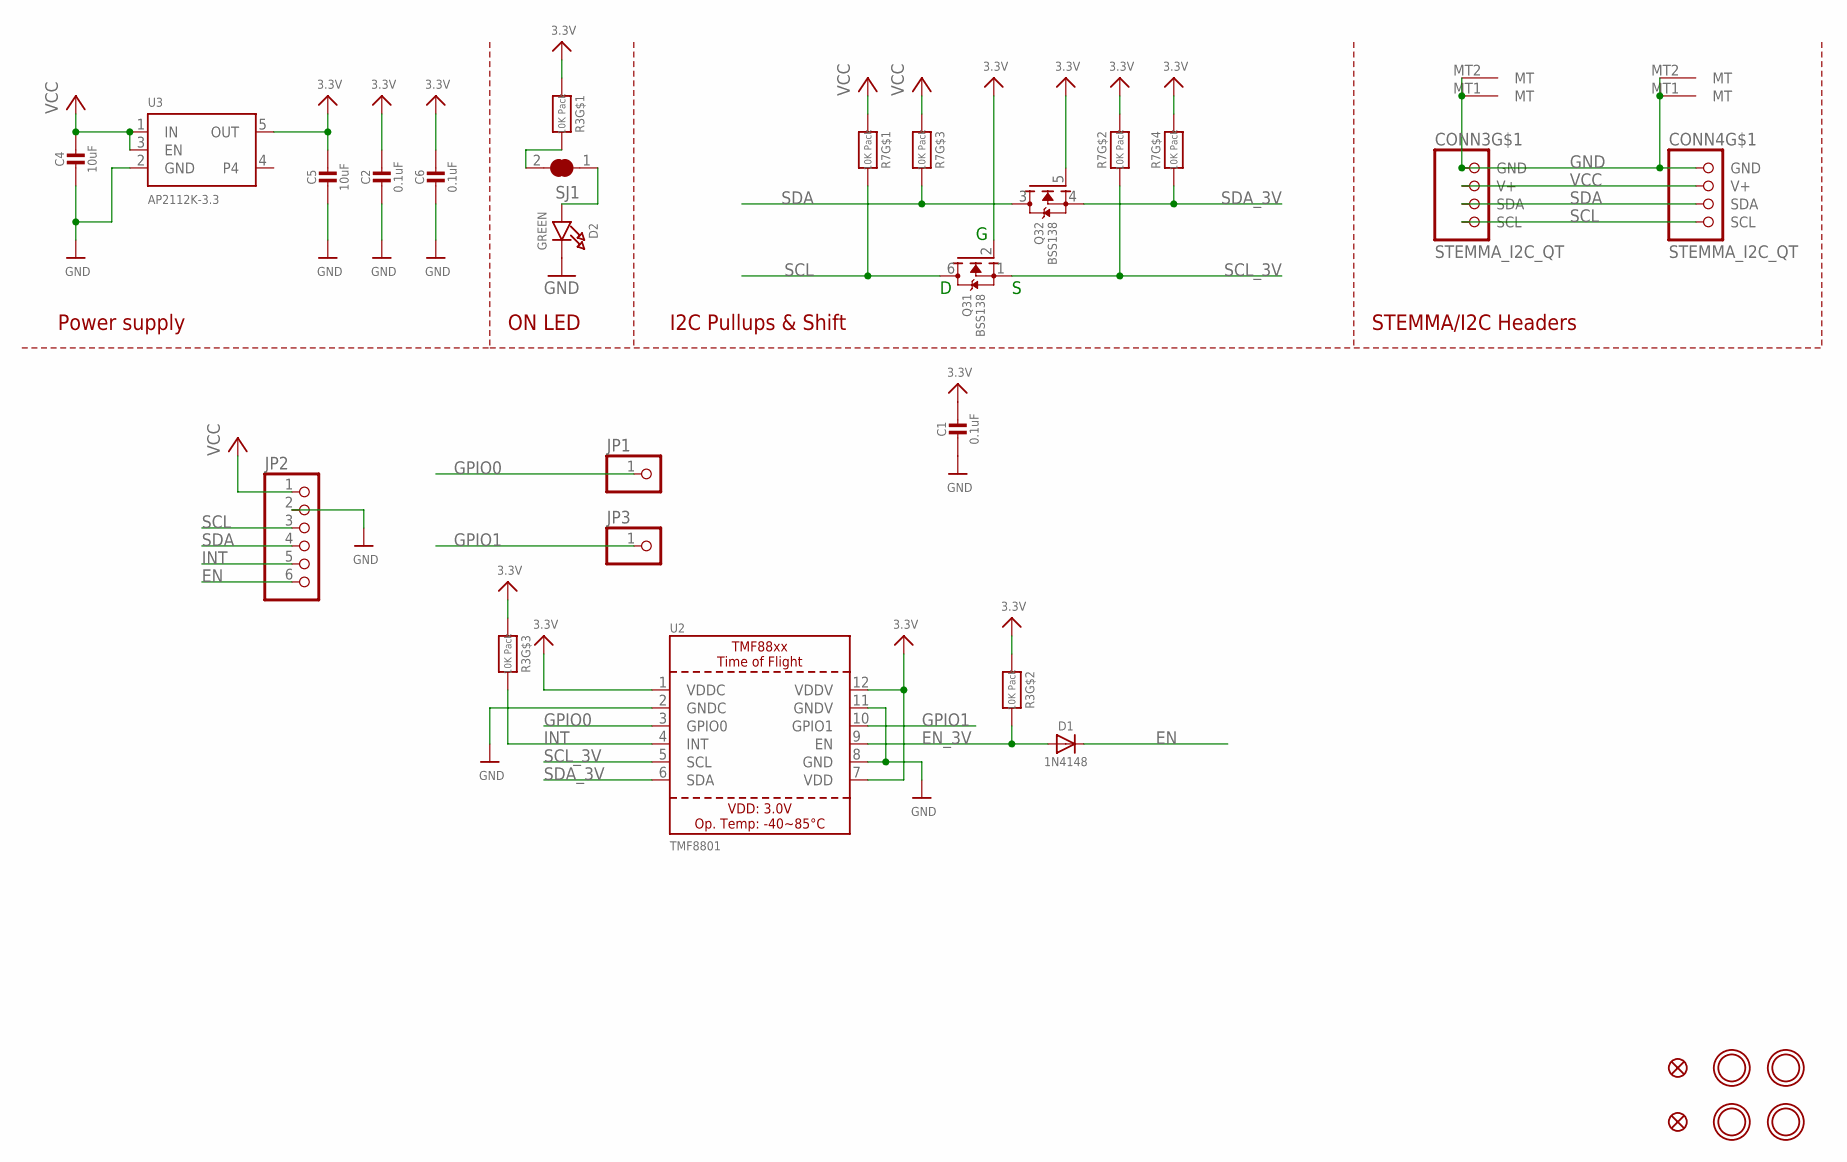
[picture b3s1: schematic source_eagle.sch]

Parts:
C1, C2, C6: 0.1uF; 0603-NO
C4, C5: 10uF; 0805-NO
CONN3, CONN4: STEMMA_I2C_QT; JST_SH4
D1: 1N4148; SOD-323
D2: GREEN; CHIPLED_0603_NOOUTLINE
FID1, FID4: FIDUCIAL_0.5MM
JP1, JP3: HEADER-1X1ROUND; 1X01_ROUND
JP2: HEADER-1X670MIL; 1X06_ROUND_70
Q3: BSS138; SOT363
R3, R7: 10K Pack; RESPACK_4X0603
SJ1: SOLDERJUMPER_CLOSED; SOLDERJUMPER_CLOSEDWIRE
U2: TMF8801; TMF880X
U3: AP2112K-3.3; SOT23-5; JLC_ROTATION 0
U$30, U$31, U$33, U$34: MOUNTINGHOLE2.5; MOUNTINGHOLE_2.5_PLATED

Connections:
3.3V: C1.1, C2.1, C5.1, C6.1, Q3.2 (G), Q3.5 (G), R3.1, R3.2 (1), R3.3 (1), R7.2 (1), R7.4 (1), U2.1 (VDDC), U2.7 (VDD), U2.12 (VDDV), U3.5 (OUT)
EN: D1.C, JP2.6
EN_3V: D1.A, R3.7 (2), U2.9 (EN)
GND: C1.2, C2.2, C4.2, C5.2, C6.2, CONN3.1 (GND), CONN3.MT1 (MT), CONN3.MT2 (MT), CONN4.1 (GND), CONN4.MT1 (MT), CONN4.MT2 (MT), D2.C, JP2.2, U2.2 (GNDC), U2.8 (GND), U2.11 (GNDV), U3.2 (GND)
GPIO0: JP1.1, U2.3 (GPIO0)
GPIO1: JP3.1, U2.10 (GPIO1)
INT: JP2.5, R3.6 (2), U2.4 (INT)
unnamed: R3.8 (2), SJ1.2
unnamed: D2.A, SJ1.1
SCL: CONN3.4 (SCL), CONN4.4 (SCL), JP2.3, Q3.6 (D), R7.8 (2)
SCL_3V: Q3.1 (S), R7.7 (2), U2.5 (SCL)
SDA: CONN3.3 (SDA), CONN4.3 (SDA), JP2.4, Q3.3 (D), R7.6 (2)
SDA_3V: Q3.4 (S), R7.5 (2), U2.6 (SDA)
VCC: C4.1, CONN3.2 (V+), CONN4.2 (V+), JP2.1, R7.1, R7.3 (1), U3.1 (IN), U3.3 (EN)

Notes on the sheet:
I2C Pullups & Shift
STEMMA/I2C Headers
ON LED
Power supply

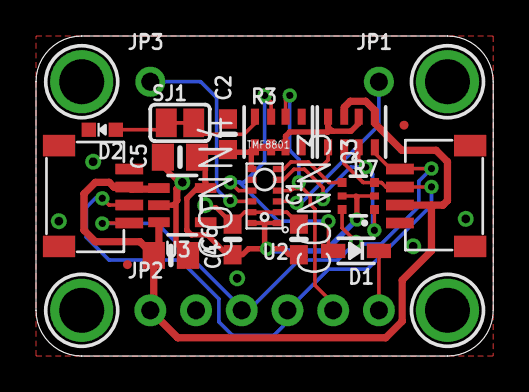
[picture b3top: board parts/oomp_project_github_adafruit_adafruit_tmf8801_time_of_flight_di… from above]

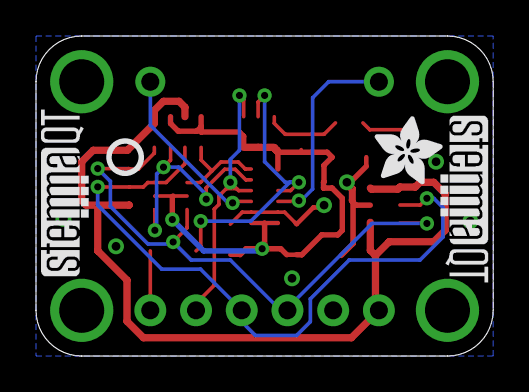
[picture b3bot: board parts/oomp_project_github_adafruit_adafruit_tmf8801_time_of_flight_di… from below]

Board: 2 copper layers, 25.4 x 17.8 mm, 43 parts (8 on the bottom side), 14 nets.

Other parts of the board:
PLABEL0: PLABEL0
PLABEL1: PLABEL1
PLABEL2: PLABEL2
PLABEL3: PLABEL3
PLABEL4: PLABEL4
PLABEL5: PLABEL5
PLABEL7: PLABEL7
PLABEL8: PLABEL8
PLABEL9: PLABEL9
PLABEL10: PLABEL10
PLABEL12: PLABEL12
PLABEL14: PLABEL14
PLABEL15: PLABEL15
PLABEL16: PLABEL16
PLABEL17: PLABEL17
U$36: ADAFRUIT_3.5MM
U$37: PCBFEAT-REV-040
U$38, U$39: STEMMAQT

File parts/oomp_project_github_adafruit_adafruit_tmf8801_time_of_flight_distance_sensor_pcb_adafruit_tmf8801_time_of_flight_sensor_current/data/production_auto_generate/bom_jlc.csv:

Comment,Designator,Footprint,LCSC Part #
,"JP1,JP3",Adafruit TMF8801 Time of Flight Sensor rev B-import-fps:1X01_ROUND,C7501259
,JP2,Adafruit TMF8801 Time of Flight Sensor rev B-import-fps:1X06_ROUND_70,C37208
,U$36,Adafruit TMF8801 Time of Flight Sensor rev B-import-fps:ADAFRUIT_3.5MM,
,U$37,Adafruit TMF8801 Time of Flight Sensor rev B-import-fps:PCBFEAT-REV-040,
,PLABEL0,Adafruit TMF8801 Time of Flight Sensor rev B-import-fps:PLABEL0,
,PLABEL1,Adafruit TMF8801 Time of Flight Sensor rev B-import-fps:PLABEL1,
,PLABEL10,Adafruit TMF8801 Time of Flight Sensor rev B-import-fps:PLABEL10,
,PLABEL12,Adafruit TMF8801 Time of Flight Sensor rev B-import-fps:PLABEL12,
,PLABEL14,Adafruit TMF8801 Time of Flight Sensor rev B-import-fps:PLABEL14,
,PLABEL15,Adafruit TMF8801 Time of Flight Sensor rev B-import-fps:PLABEL15,
,PLABEL16,Adafruit TMF8801 Time of Flight Sensor rev B-import-fps:PLABEL16,
,PLABEL17,Adafruit TMF8801 Time of Flight Sensor rev B-import-fps:PLABEL17,
,PLABEL2,Adafruit TMF8801 Time of Flight Sensor rev B-import-fps:PLABEL2,
,PLABEL3,Adafruit TMF8801 Time of Flight Sensor rev B-import-fps:PLABEL3,
,PLABEL4,Adafruit TMF8801 Time of Flight Sensor rev B-import-fps:PLABEL4,
,PLABEL5,Adafruit TMF8801 Time of Flight Sensor rev B-import-fps:PLABEL5,
,PLABEL7,Adafruit TMF8801 Time of Flight Sensor rev B-import-fps:PLABEL7,
,PLABEL8,Adafruit TMF8801 Time of Flight Sensor rev B-import-fps:PLABEL8,
,PLABEL9,Adafruit TMF8801 Time of Flight Sensor rev B-import-fps:PLABEL9,
,"U$38,U$39",Adafruit TMF8801 Time of Flight Sensor rev B-import-fps:STEMMAQT,
0.1uF,"C1,C2,C6",Adafruit TMF8801 Time of Flight Sensor rev B-import-fps:0603-NO,C14663
10K Pack,"R3,R7",Adafruit TMF8801 Time of Flight Sensor rev B-import-fps:RESPACK_4X0603,C98220
10uF,"C4,C5",Adafruit TMF8801 Time of Flight Sensor rev B-import-fps:0805-NO,
1N4148,D1,Adafruit TMF8801 Time of Flight Sensor rev B-import-fps:SOD-323,
AP2112K-3.3,U3,Adafruit TMF8801 Time of Flight Sensor rev B-import-fps:SOT23-5,
BSS138,Q3,Adafruit TMF8801 Time of Flight Sensor rev B-import-fps:SOT363,
GREEN,D2,Adafruit TMF8801 Time of Flight Sensor rev B-import-fps:CHIPLED_0603_NOOUTLINE,
STEMMA_I2C_QT,"CONN3,CONN4",Adafruit TMF8801 Time of Flight Sensor rev B-import-fps:JST_SH4,C160404
TMF8801,U2,Adafruit TMF8801 Time of Flight Sensor rev B-import-fps:TMF880X,

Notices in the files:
parts and their libraries:
adafruit_sensor: COPYRIGHT: Copyright (C) 2025 Ultra Librarian. All rights reserved.
microbuilder: This work is placed in the public domain, and may be freely used for commercial and non-commercial work with the following conditions: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
SparkFun-Aesthetics: Released under the Creative Commons
